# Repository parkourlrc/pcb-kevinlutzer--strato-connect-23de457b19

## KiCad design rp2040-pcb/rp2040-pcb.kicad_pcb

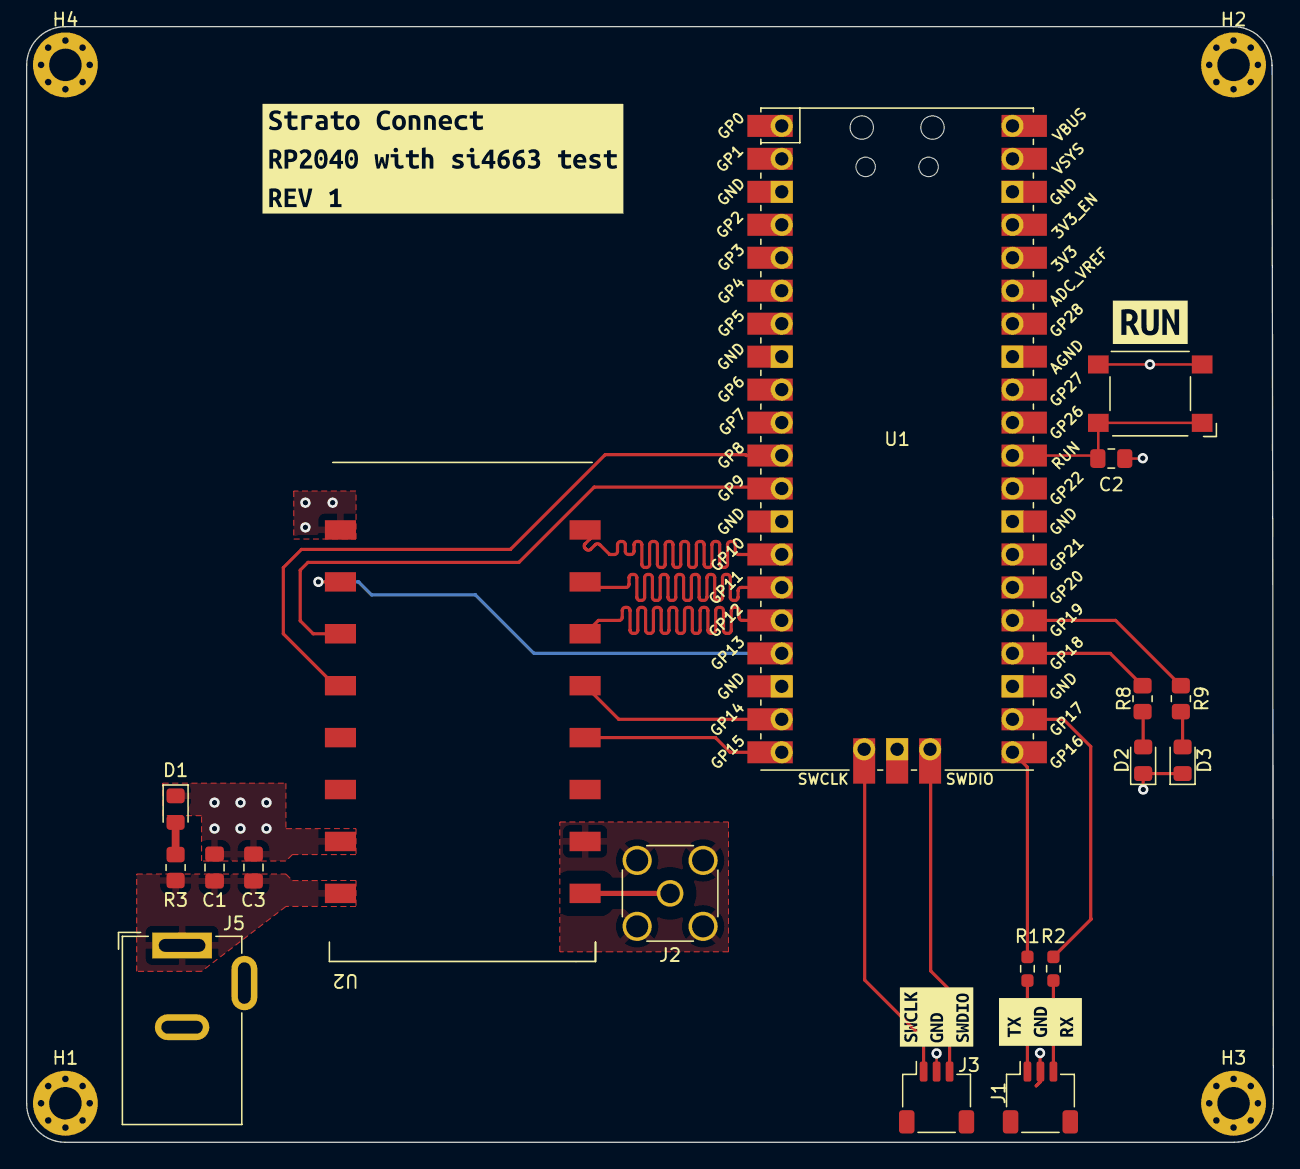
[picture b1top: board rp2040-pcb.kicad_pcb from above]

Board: 2 copper layers, 96.1 x 86.0 mm, 26 parts (0 on the bottom side), 24 nets.

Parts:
C1, C2, C3: C; C_0805_2012Metric_Pad1.18x1.45mm_HandSolder
D1, D2, D3: LED; LED_0805_2012Metric_Pad1.15x1.40mm_HandSolder
H1, H2, H3, H4: MountingHole_Pad; MountingHole_2.5mm_Pad_Via
J1, J3: Conn_01x03_Pin; JST_SH_SM03B-SRSS-TB_1x03-1MP_P1.00mm_Horizontal
J2: Conn_Coaxial; SMA_Wurth_60312002114503_Vertical
J5: Barrel_Jack; BarrelJack_GCT_DCJ200-10-A_Horizontal
R1, R2: 100; R_0603_1608Metric_Pad0.98x0.95mm_HandSolder
R3, R8, R9: 220; R_0805_2012Metric_Pad1.20x1.40mm_HandSolder
SW1: SW_SPST; SW_SPST_Omron_B3FS-100xP
U1: Pico; RPi_Pico_SMD_TH
U2: RF4463F30
kibuzzard-654DA24D: G***; kibuzzard-654DA24D
kibuzzard-654DAC3C: G***; kibuzzard-654DAC3C
kibuzzard-654DC7E1: G***; kibuzzard-654DC7E1
kibuzzard-696C09E5: G***; kibuzzard-696C09E5

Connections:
+VDC: C1.1, C3.1, J5.1, R3.1, U2.16 (VCC)
/RF_GND: J2.2 (Ext), U2.2 (ANT_GND)
GND: C1.2, C2.2, C3.2, D1.1 (K), D2.1 (K), D3.1 (K), H1.1, H2.1, H3.1, H4.1, J1.2, J3.2, J5.2, SW1.2 (B), U1.3 (GND), U1.8 (GND), U1.13 (GND), U1.18 (GND), U1.23 (GND), U1.28 (GND), U1.33 (AGND), U1.37 (3V3_EN), U1.38 (GND), U1.42 (GND), U2.9 (GND), U2.15 (GND)
GPIO0: U1.20 (GPIO15), U2.4 (GPIO0)
GPIO1: U1.19 (GPIO14), U2.5 (GPIO1)
LED1: R8.1, U1.24 (GPIO18)
LED2: R9.1, U1.25 (GPIO19)
unnamed: D1.2 (A), R3.2
unnamed: D2.2 (A), R8.2
unnamed: D3.2 (A), R9.2
unnamed: J1.1, R1.1
unnamed: J1.3, R2.1
unnamed: J2.1 (In), U2.1 (ANT)
RUN: C2.1, SW1.1 (A), U1.30 (RUN)
SDN: U1.11 (GPIO8), U2.12 (SDN)
SPI1_MISO: U1.16 (GPIO12), U2.6 (SDO)
SPI1_MOSI: U1.15 (GPIO11), U2.7 (SDI)
SPI1_SCK: U1.14 (GPIO10), U2.8 (SCLK)
SWCLK: J3.1, U1.41 (SWCLK)
SWDIO: J3.3, U1.43 (SWDIO)
UART_RX: R2.2, U1.22 (GPIO17)
UART_TX: R1.2, U1.21 (GPIO16)
~IRQ: U1.12 (GPIO9), U2.11 (~IRQ)
~SPI1_CS: U1.17 (GPIO13), U2.10 (~SEL)

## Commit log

2026-03-04 add the rev-a fab files
